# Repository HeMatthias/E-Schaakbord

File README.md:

# **♔E-Schaakbord♔**

>#### Gemaakt door: *Hendrickx Matthias*

## Beschrijving

Het E-schaakbord is een elektronisch schaakbord dat a.d.h.v. verschillende elektronica componenten zoals RGB LED’s, sensoren, ... je interactief leert schaken.

Doordat de vakken onder de pionnen belicht worden is er de mogelijkheid om aan te tonen welke stap de pion kan zetten die men opheft of om weer te geven welke er kunnen geslagen worden.

Er bevindt zich ook rechts van het E-schaakbord 2 klokken/timers (7-segmenten) die men eventueel kan instellen hoeveel tijd iedere persoon kan spelen.

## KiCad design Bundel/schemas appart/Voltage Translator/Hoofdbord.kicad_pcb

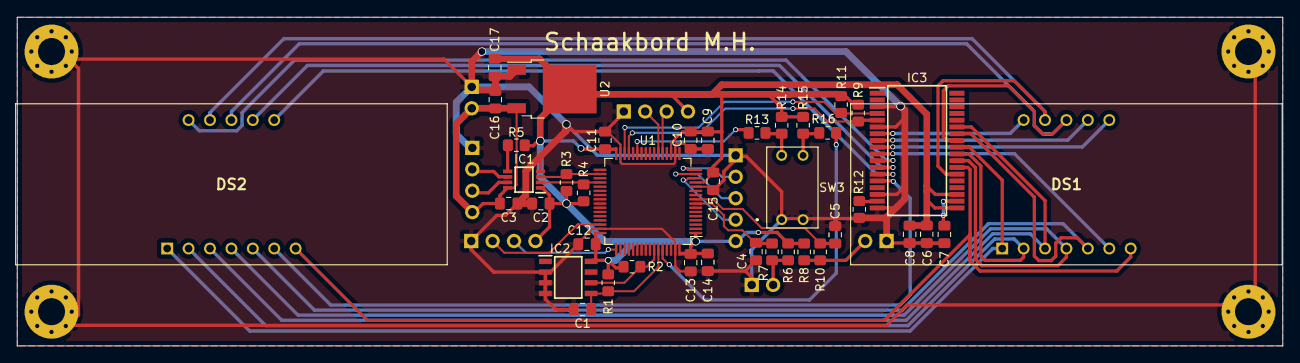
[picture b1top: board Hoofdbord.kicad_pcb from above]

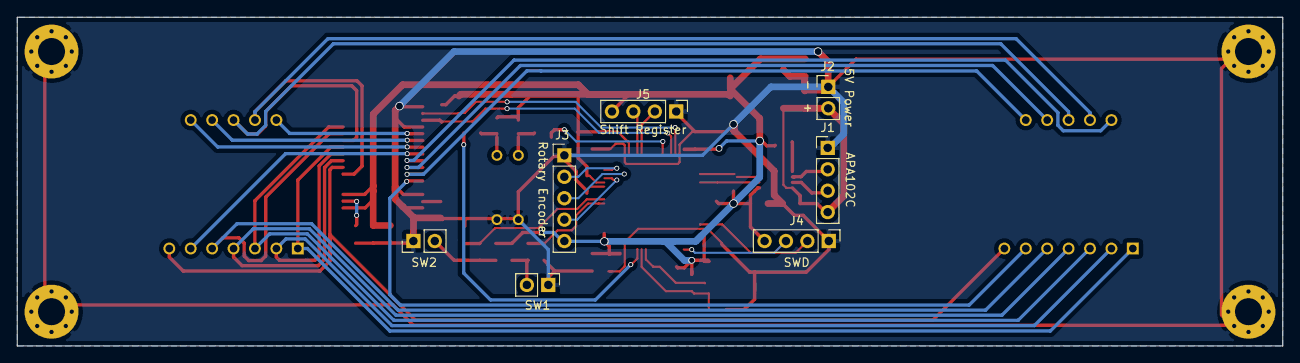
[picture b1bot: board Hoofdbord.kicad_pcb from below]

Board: 2 copper layers, 150.1 x 39.0 mm, 48 parts (7 on the bottom side), 45 nets.

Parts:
C1, C7: 22pF; C_0805_2012Metric_Pad1.18x1.45mm_HandSolder
C2, C3, C14: 1µF; C_0805_2012Metric_Pad1.18x1.45mm_HandSolder
C4, C5, C8, C10, C11, C12, C13, C15: 100nF; C_0805_2012Metric_Pad1.18x1.45mm_HandSolder
C6: 47µF; C_0805_2012Metric_Pad1.18x1.45mm_HandSolder
C9, C16, C17: 10µF; C_0805_2012Metric_Pad1.18x1.45mm_HandSolder
DS1, DS2: HDSP-B03G; HDSPB03G
IC1: SN74LVC2T45DCTRE4; SOP65P400X130-8N
IC2: M24C04-RMN6TP; SOIC127P600X175-8N
IC3: MAX6955AAX+; SOP80P1030X264-36N
J1: APA102C; PinHeader_1x04_P2.54mm_Vertical
J2: 5V Power; PinHeader_1x02_P2.54mm_Vertical
J3: Rotary Encoder; PinHeader_1x05_P2.54mm_Vertical
J4: SWD; PinHeader_1x04_P2.54mm_Vertical
J5: Shift Register; PinHeader_1x04_P2.54mm_Vertical
R1, R2, R3, R4, R5, R6, R7, R8, R9, R10, R11, R13, R14, R15, R16: 10k; R_0805_2012Metric_Pad1.20x1.40mm_HandSolder
R12: 56k; R_0805_2012Metric_Pad1.20x1.40mm_HandSolder
SW1, SW2: SW_Push; PinHeader_1x02_P2.54mm_Vertical
SW3: Boot Modes; 418117270902
U1: STM32F101RDTx; LQFP-64_10x10mm_P0.5mm
U2: NCP1117-3.3_TO252; TO-252-2

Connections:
+3V3: C2.2, C6.2, C8.1, C9.2, C10.2, C11.2, C12.2, C13.2, C14.2, C15.2, C17.1, IC1.1, IC2.8, IC3.19, IC3.21, J3.5, J4.4, J5.4, R1.2, R2.2, R3.2, R4.2, R5.1, R6.2, R8.2, R9.1, R11.2, R14.2, R15.1, U1.1, U1.13, U1.19, U1.32, U1.48, U1.64, U2.2
+5V: C3.1, C16.2, IC1.8, J1.4, J2.2, U2.3
BOOT0: R16.2, U1.60
BOOT1: R13.2, U1.27
GND: C1.1, C2.1, C3.2, C4.2, C5.2, C6.1, C7.1, C8.2, C9.1, C10.1, C11.1, C12.1, C13.1, C14.1, C15.1, C16.1, C17.2, IC1.4, IC2.2, IC2.3, IC2.4, IC3.3, IC3.6, IC3.16, IC3.18, J1.1, J2.1, J3.1, J4.1, J5.1, R12.2, SW1.1, SW2.1, SW3.1, SW3.2, U1.12, U1.18, U1.31, U1.47, U1.63, U2.1
unnamed: C7.2, IC3.20
unnamed: IC1.5, R5.2
unnamed: IC1.6, J1.2
unnamed: IC1.7, J1.3
unnamed: IC3.17, R12.1
unnamed: R6.1, R7.2, SW1.2
unnamed: R8.1, R10.2, SW2.2
unnamed: R13.1, R14.1, SW3.4
unnamed: R15.2, R16.1, SW3.3
O0: DS1.12, IC3.7
O1: DS1.9, IC3.8
O2: DS1.8, IC3.9
O3: DS1.6, IC3.10
O4: DS2.12, IC3.11
O5: DS2.9, IC3.12
O6: DS2.8, IC3.13
O7: DS2.6, IC3.14
O11: DS1.11, DS2.11, IC3.24
O12: DS1.7, DS2.7, IC3.25
O13: DS1.4, DS2.4, IC3.26
O14: DS1.2, DS2.2, IC3.27
O15: DS1.1, DS2.1, IC3.28
O16: DS1.10, DS2.10, IC3.29
O17: DS1.5, DS2.5, IC3.30
O18: DS1.3, DS2.3, IC3.31
PA0: J3.4, U1.14
PA1: J3.3, U1.15
PA2: J3.2, U1.16
PA5: J5.3, U1.21
PA6: J5.2, U1.22
PA13: J4.2, U1.46
PA14: J4.3, U1.49
PB6: IC2.6, R2.1, U1.58
PB7: C1.2, IC2.5, R1.1, U1.59
PB10: IC3.5, R9.2, U1.29
PB11: IC3.4, R11.1, U1.30
PB13: IC1.3, R3.1, U1.34
PB15: IC1.2, R4.1, U1.36
PC0: C4.1, R7.1, U1.8
PC1: C5.1, R10.1, U1.9

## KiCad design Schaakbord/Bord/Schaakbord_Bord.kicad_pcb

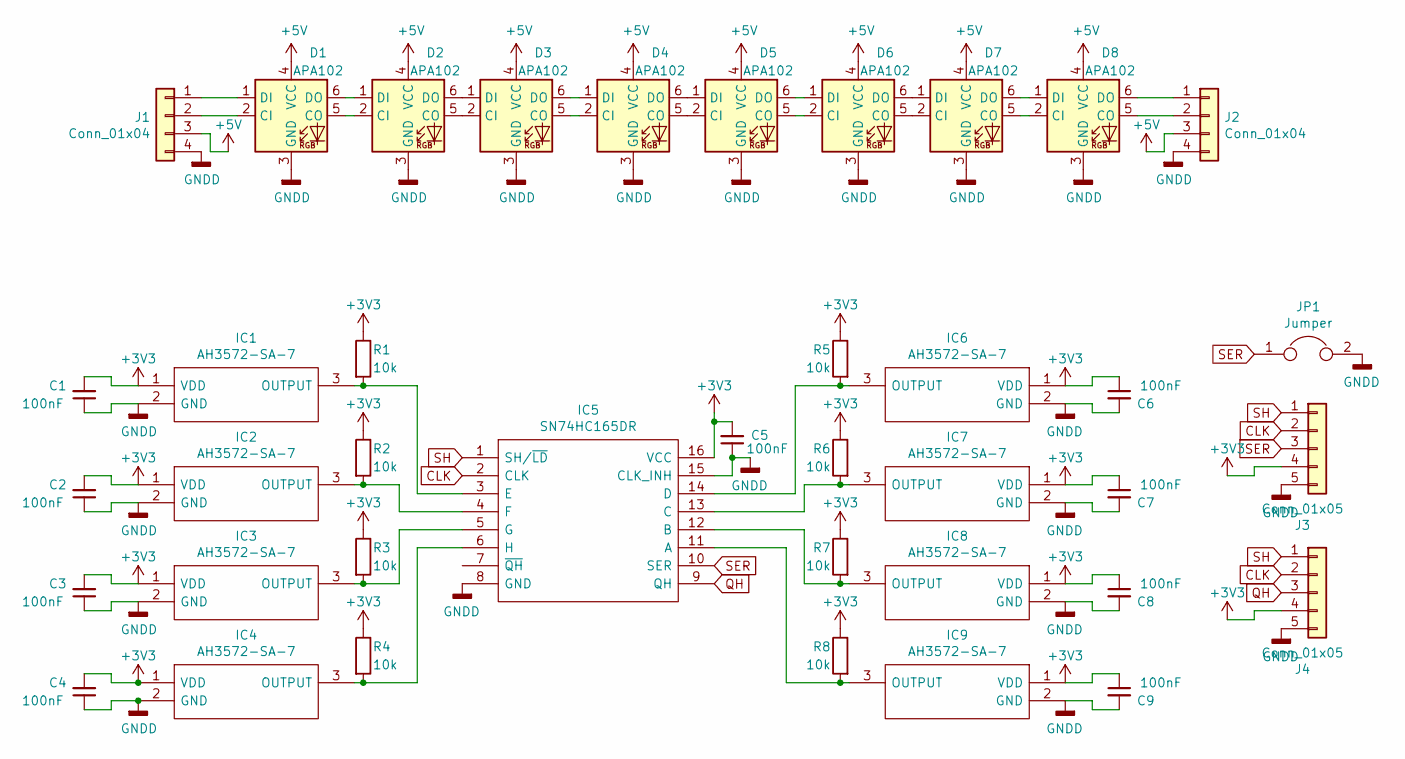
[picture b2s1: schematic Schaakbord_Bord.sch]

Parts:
C1, C2, C3, C4, C5, C6, C7, C8, C9: 100nF; C_0805_2012Metric_Pad1.18x1.45mm_HandSolder
D1, D2, D3, D4, D5, D6, D7, D8: APA102; LED_RGB_5050-6
IC1, IC2, IC3, IC4, IC6, IC7, IC8, IC9: AH3572-SA-7; SOT-23_Handsoldering; Mouser Part Number 621-AH3572-SA-7
IC5: SN74HC165DR; SOIC127P600X175-16N; Mouser Part Number 595-SN74HC165DR
J1: Conn_01x04; PinHeader_1x04_P2.54mm_Horizontal
J2: Conn_01x04; PinSocket_1x04_P2.54mm_Horizontal
J3: Conn_01x05; PinHeader_1x05_P2.54mm_Horizontal
J4: Conn_01x05; PinSocket_1x05_P2.54mm_Horizontal
JP1: Jumper; SolderJumper-2_P1.3mm_Open_TrianglePad1.0x1.5mm
R1, R2, R3, R4, R5, R6, R7, R8: 10k; R_0805_2012Metric_Pad1.20x1.40mm_HandSolder

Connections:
+3V3: C1.2, C2.2, C3.2, C4.2, C5.2, C6.1, C7.1, C8.1, C9.1, IC1.1 (VDD), IC2.1 (VDD), IC3.1 (VDD), IC4.1 (VDD), IC5.16 (VCC), IC6.1 (VDD), IC7.1 (VDD), IC8.1 (VDD), IC9.1 (VDD), J3.4, J4.4, R1.1, R2.1, R3.1, R4.1, R5.1, R6.1, R7.1, R8.1
+5V: D1.4 (VCC), D2.4 (VCC), D3.4 (VCC), D4.4 (VCC), D5.4 (VCC), D6.4 (VCC), D7.4 (VCC), D8.4 (VCC), J1.3, J2.3
CLK: IC5.2 (CLK), J3.2, J4.2
GNDD: C1.1, C2.1, C3.1, C4.1, C5.1, C6.2, C7.2, C8.2, C9.2, D1.3 (GND), D2.3 (GND), D3.3 (GND), D4.3 (GND), D5.3 (GND), D6.3 (GND), D7.3 (GND), D8.3 (GND), IC1.2 (GND), IC2.2 (GND), IC3.2 (GND), IC4.2 (GND), IC5.8 (GND), IC5.15 (CLK_INH), IC6.2 (GND), IC7.2 (GND), IC8.2 (GND), IC9.2 (GND), J1.4, J2.4, J3.5, J4.5, JP1.2
unnamed: D1.1 (DI), J1.1
unnamed: D1.2 (CI), J1.2
unnamed: D1.5 (CO), D2.2 (CI)
unnamed: D1.6 (DO), D2.1 (DI)
unnamed: D2.5 (CO), D3.2 (CI)
unnamed: D2.6 (DO), D3.1 (DI)
unnamed: D3.5 (CO), D4.2 (CI)
unnamed: D3.6 (DO), D4.1 (DI)
unnamed: D4.5 (CO), D5.2 (CI)
unnamed: D4.6 (DO), D5.1 (DI)
unnamed: D5.5 (CO), D6.2 (CI)
unnamed: D5.6 (DO), D6.1 (DI)
unnamed: D6.5 (CO), D7.2 (CI)
unnamed: D6.6 (DO), D7.1 (DI)
unnamed: D7.5 (CO), D8.2 (CI)
unnamed: D7.6 (DO), D8.1 (DI)
unnamed: D8.5 (CO), J2.2
unnamed: D8.6 (DO), J2.1
unnamed: IC1.3 (OUTPUT), IC5.3 (E), R1.2
unnamed: IC2.3 (OUTPUT), IC5.4 (F), R2.2
unnamed: IC3.3 (OUTPUT), IC5.5 (G), R3.2
unnamed: IC4.3 (OUTPUT), IC5.6 (H), R4.2
unnamed: IC5.11 (A), IC9.3 (OUTPUT), R8.2
unnamed: IC5.12 (B), IC8.3 (OUTPUT), R7.2
unnamed: IC5.13 (C), IC7.3 (OUTPUT), R6.2
unnamed: IC5.14 (D), IC6.3 (OUTPUT), R5.2
QH: IC5.9 (QH), J4.3
SER: IC5.10 (SER), J3.3, JP1.1
SH: IC5.1 (SH/~LD), J3.1, J4.1

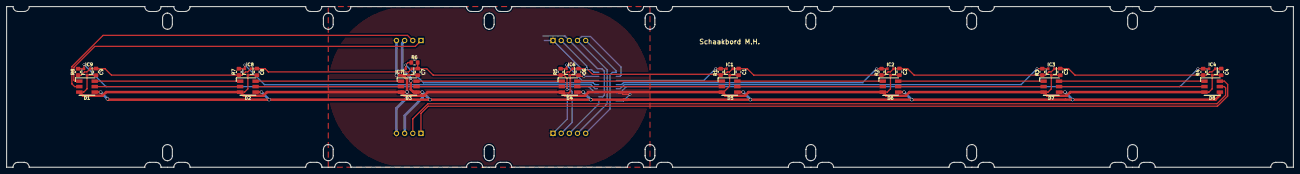
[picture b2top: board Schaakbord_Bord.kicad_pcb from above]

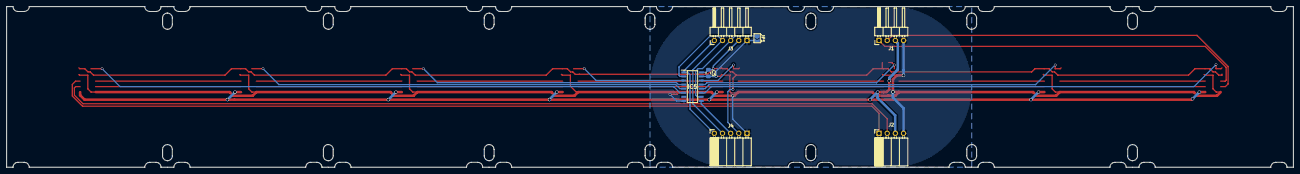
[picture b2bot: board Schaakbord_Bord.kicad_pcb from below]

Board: 2 copper layers, 400.3 x 50.0 mm, 39 parts (7 on the bottom side), 33 nets.

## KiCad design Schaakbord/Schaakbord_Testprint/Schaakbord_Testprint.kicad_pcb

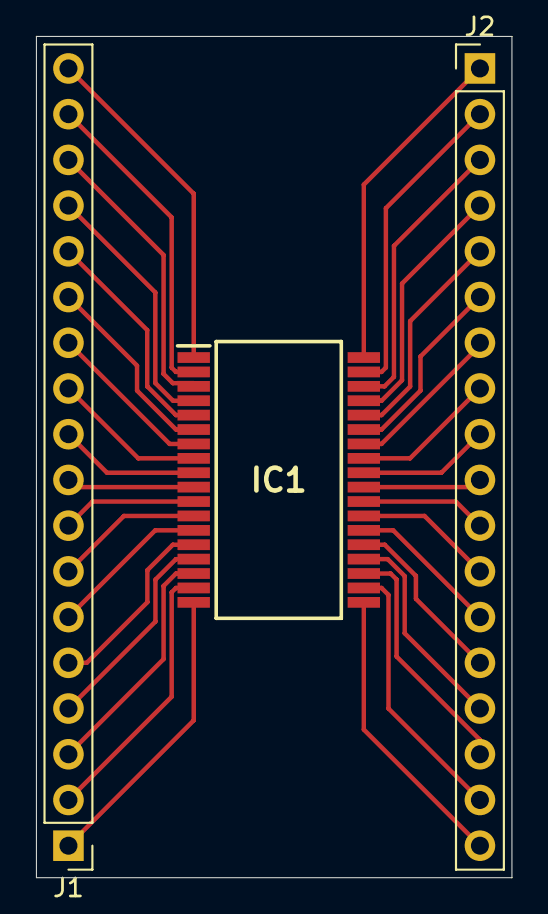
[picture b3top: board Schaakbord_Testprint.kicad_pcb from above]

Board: 2 copper layers, 26.4 x 46.7 mm, 3 parts (0 on the bottom side), 36 nets.

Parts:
IC1: MAX6955AAX+; SOP80P1030X264-36N
J1, J2: Conn_01x18_MountingPin; PinHeader_1x18_P2.54mm_Vertical

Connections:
unnamed: IC1.1, J1.18
unnamed: IC1.2, J1.17
unnamed: IC1.3, J1.16
unnamed: IC1.4, J1.15
unnamed: IC1.5, J1.14
unnamed: IC1.6, J1.13
unnamed: IC1.7, J1.12
unnamed: IC1.8, J1.11
unnamed: IC1.9, J1.10
unnamed: IC1.10, J1.9
unnamed: IC1.11, J1.8
unnamed: IC1.12, J1.7
unnamed: IC1.13, J1.6
unnamed: IC1.14, J1.5
unnamed: IC1.15, J1.4
unnamed: IC1.16, J1.3
unnamed: IC1.17, J1.2
unnamed: IC1.18, J1.1
unnamed: IC1.19, J2.18
unnamed: IC1.20, J2.17
unnamed: IC1.21, J2.16
unnamed: IC1.22, J2.15
unnamed: IC1.23, J2.14
unnamed: IC1.24, J2.13
unnamed: IC1.25, J2.12
unnamed: IC1.26, J2.11
unnamed: IC1.27, J2.10
unnamed: IC1.28, J2.9
unnamed: IC1.29, J2.8
unnamed: IC1.30, J2.7
unnamed: IC1.31, J2.6
unnamed: IC1.32, J2.5
unnamed: IC1.33, J2.4
unnamed: IC1.34, J2.3
unnamed: IC1.35, J2.2
unnamed: IC1.36, J2.1

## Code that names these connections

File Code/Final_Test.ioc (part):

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Mcu.Name=STM32F101R(C-D-E)Tx
Mcu.Package=LQFP64
Mcu.UserName=STM32F101RDTx
PA0-WKUP.Signal=S_TIM2_CH1_ETR
PA1.Signal=S_TIM2_CH2
PA13.Mode=Serial_Wire
PA13.Signal=SYS_JTMS-SWDIO
PA14.Mode=Serial_Wire
PA14.Signal=SYS_JTCK-SWCLK
PA2.GPIOParameters=GPIO_Speed,GPIO_Label
PA2.GPIO_Label=SPI1_CS
PA2.GPIO_Speed=GPIO_SPEED_FREQ_HIGH
PA2.Signal=GPIO_Output
PA5.GPIOParameters=GPIO_Speed,GPIO_Label
PA5.GPIO_Label=SPI1_CLK
PA5.GPIO_Speed=GPIO_SPEED_FREQ_HIGH
PA5.Signal=GPIO_Output
PA6.GPIOParameters=GPIO_Label
PA6.GPIO_Label=SPI1_MISO
PA6.Signal=GPIO_Input
PB10.Mode=I2C
PB10.Signal=I2C2_SCL
PB11.Mode=I2C
PB11.Signal=I2C2_SDA
PB13.GPIOParameters=GPIO_Speed,GPIO_Label
PB13.GPIO_Label=SPI2_SCK
PB13.GPIO_Speed=GPIO_SPEED_FREQ_HIGH
PB13.Signal=GPIO_Output
PB15.GPIOParameters=GPIO_Speed,GPIO_PuPd,GPIO_Label
PB15.GPIO_Label=SPI2_MOSI
PB15.GPIO_PuPd=GPIO_NOPULL
PB15.GPIO_Speed=GPIO_SPEED_FREQ_HIGH
PB15.Signal=GPIO_Output
PB6.Mode=I2C
PB6.Signal=I2C1_SCL
PB7.Mode=I2C
PB7.Signal=I2C1_SDA
PC0.GPIOParameters=GPIO_Label,GPIO_ModeDefaultEXTI
PC0.GPIO_Label=SWR
PC0.GPIO_ModeDefaultEXTI=GPIO_MODE_IT_FALLING
PC0.Signal=GPXTI0
PC1.GPIOParameters=GPIO_Label,GPIO_ModeDefaultEXTI
PC1.GPIO_Label=SWL
PC1.GPIO_ModeDefaultEXTI=GPIO_MODE_IT_FALLING
PC1.Signal=GPXTI1
RCC.SYSCLKFreq_VALUE=36000000
RCC.SYSCLKSource=RCC_SYSCLKSOURCE_PLLCLK
board=custom

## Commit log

2021-03-07 files -> Pionnen
2021-03-08 Ontwerp
2021-03-23 Meeting Shift Register
2021-03-23 Update Schema
2021-04-12 Update schematic
2021-04-15 Schematic Update
2021-04-22 Update PCB
2021-04-26 Ontwerp Update
2021-05-19 Lot's of changes
2021-05-25 Code
2021-05-27 Code met PPT
